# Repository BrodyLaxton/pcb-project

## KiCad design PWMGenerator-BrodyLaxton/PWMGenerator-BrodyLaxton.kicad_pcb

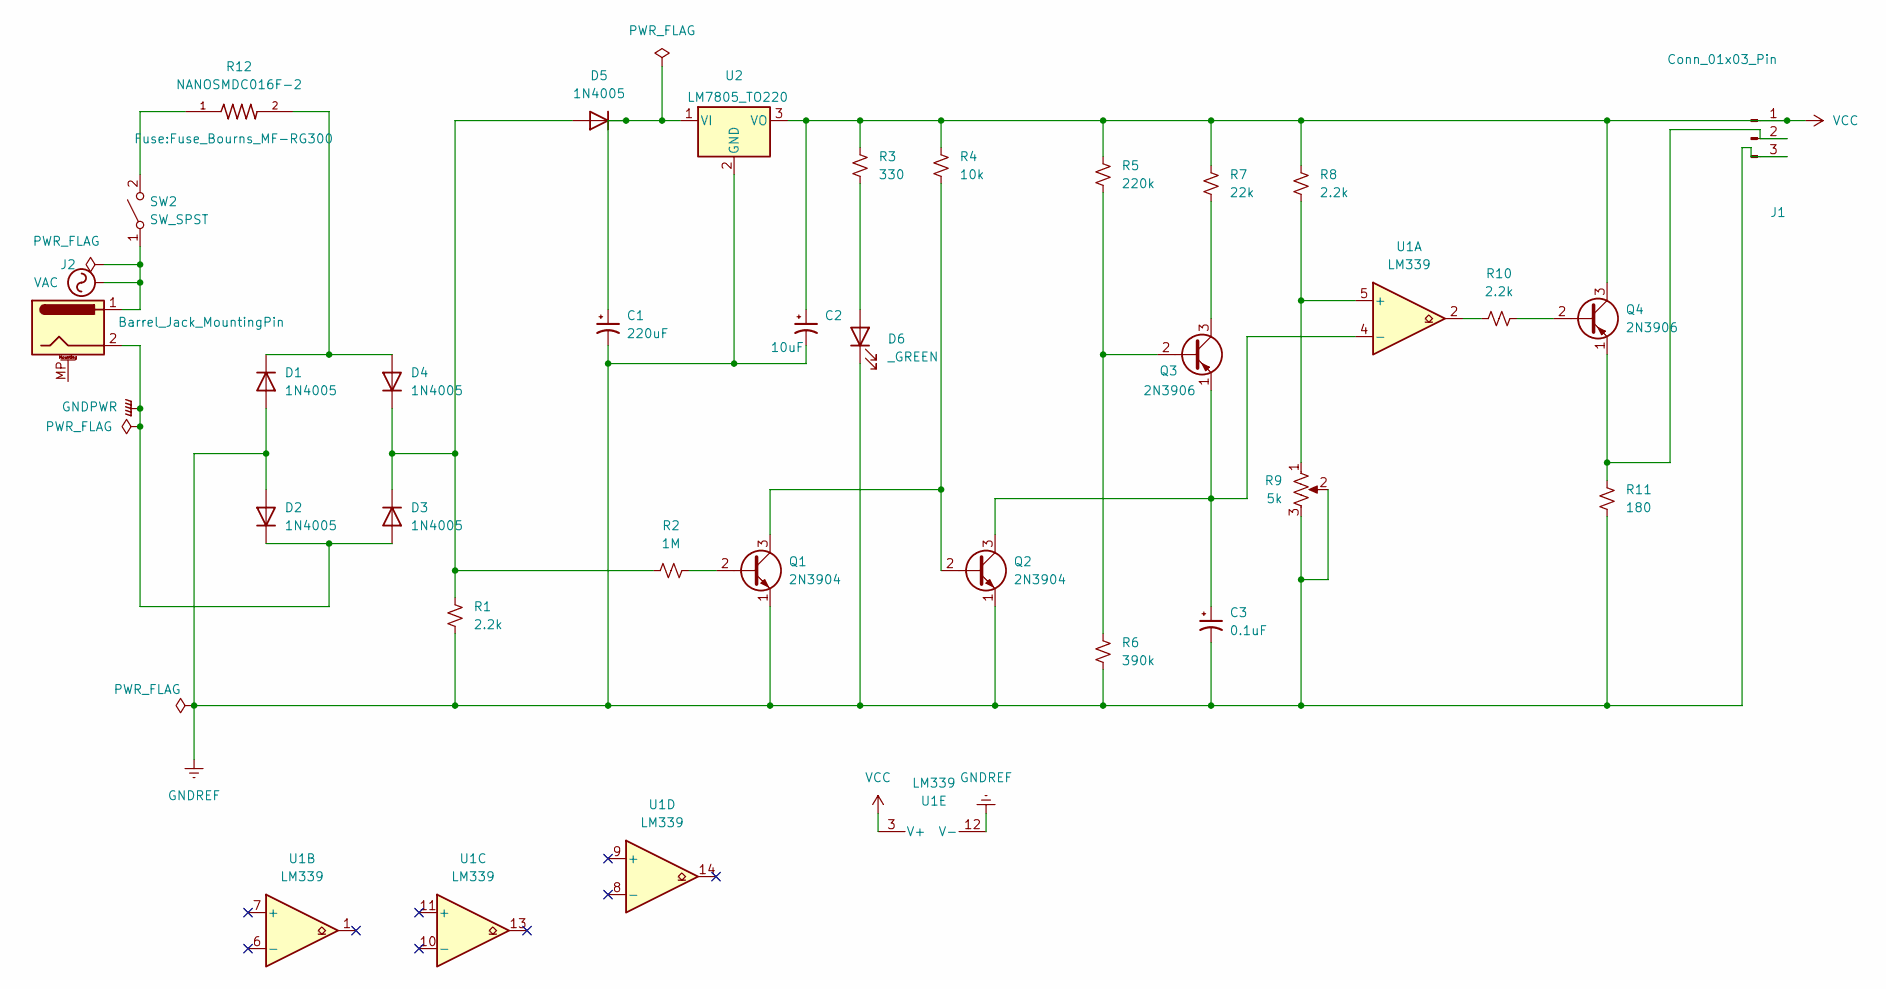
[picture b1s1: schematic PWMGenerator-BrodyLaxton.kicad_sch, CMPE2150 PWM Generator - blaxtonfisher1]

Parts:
C1: 220uF; CP_Radial_D10.0mm_P5.00mm
C2: 10uF; CP_Radial_D10.0mm_P5.00mm
C3: 0.1uF; C_0805_2012Metric_Pad1.18x1.45mm_HandSolder
D1, D2, D3, D4, D5: 1N4005; D_0805_2012Metric_Pad1.15x1.40mm_HandSolder
D6: _GREEN; LED_D5.0mm
J1: Conn_01x03_Pin; PinHeader_1x03_P2.54mm_Horizontal
J2: Barrel_Jack_MountingPin; BarrelJack_Wuerth_694106106102_2.0x5.5mm
Q1, Q2: 2N3904; SOT-23
Q3, Q4: 2N3906; SOT-23
R1, R8, R10: 2.2k; R_0805_2012Metric
R2: 1M; R_0805_2012Metric
R3: 330; R_0805_2012Metric
R4: 10k; R_0805_2012Metric
R5: 220k; R_0805_2012Metric
R6: 390k; R_0805_2012Metric
R7: 22k; R_0805_2012Metric
R9: 5k; Potentiometer_ACP_CA6-H2,5_Horizontal
R11: 180; R_0805_2012Metric
R12: NANOSMDC016F-2; Fuse_Bourns_MF-RG300
SW2: SW_SPST; SW_DIP_SPSTx01_Slide_9.78x4.72mm_W8.61mm_P2.54mm
U1: LM339; SOIC-14_3.9x8.7mm_P1.27mm
U2: LM7805_TO220; TO-220-3_Vertical

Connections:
GNDPWR: D2.1 (K), D3.2 (A), J2.2
GNDREF: C1.2, C2.2, C3.2, D1.2 (A), D2.2 (A), D6.1 (K), J1.3, Q1.1 (E), Q2.1 (E), R1.2, R6.2, R9.2, R9.3, R11.2, U1.12 (V-), U2.2 (GND)
unnamed: D1.1 (K), D4.2 (A), R12.2
unnamed: D3.1 (K), D4.1 (K), D5.2 (A), R1.1, R2.1
unnamed: C1.1, D5.1 (K), U2.1 (VI)
unnamed: D6.2 (A), R3.2
unnamed: J1.2, Q4.1 (E), R11.1
unnamed: Q1.2 (B), R2.2
unnamed: Q1.3 (C), Q2.2 (B), R4.2
unnamed: C3.1, Q2.3 (C), Q3.1 (E), U1.4 (-)
unnamed: Q3.2 (B), R5.1, R6.1
unnamed: Q3.3 (C), R7.2
unnamed: Q4.2 (B), R10.2
unnamed: R10.1, U1.2
unnamed: R12.1, SW2.2 (B)
unnamed: R8.2, R9.1, U1.5 (+)
VAC: J2.1, SW2.1 (A)
VCC: C2.1, J1.1, Q4.3 (C), R3.1, R4.1, R5.2, R7.1, R8.1, U1.3 (V+), U2.3 (VO)

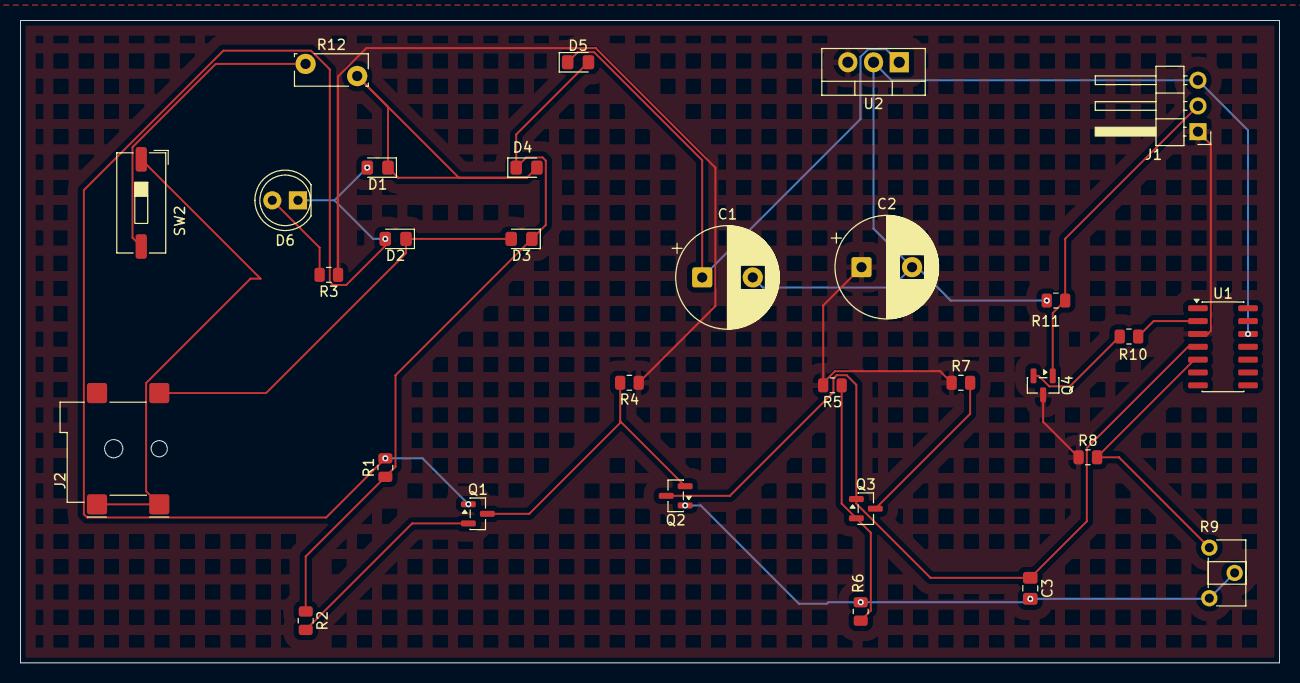
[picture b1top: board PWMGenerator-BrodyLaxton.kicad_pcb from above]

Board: 2 copper layers, 124.5 x 63.5 mm, 30 parts (0 on the bottom side), 18 nets.

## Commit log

2025-12-07 push1
    Start
2025-12-07 iuyt
    [-098
2025-12-09 4
    09
2025-12-13 project b b part1
    xdbg
2025-12-13 projectb part 3
    finsihed
2025-12-15 project2 updated
    had to update the polyfuse sylmbol
2025-12-15 PROJECT 3
    part 1
2025-12-15 part1
    oituy
2025-12-15 project 3
    part 2 done
2025-12-15 part 2 revised
2025-12-15 part3
    not entirely sure this is doner correctly
2025-12-15 PART 2 REDONE
2025-12-15 part 4
    part 4 complete
